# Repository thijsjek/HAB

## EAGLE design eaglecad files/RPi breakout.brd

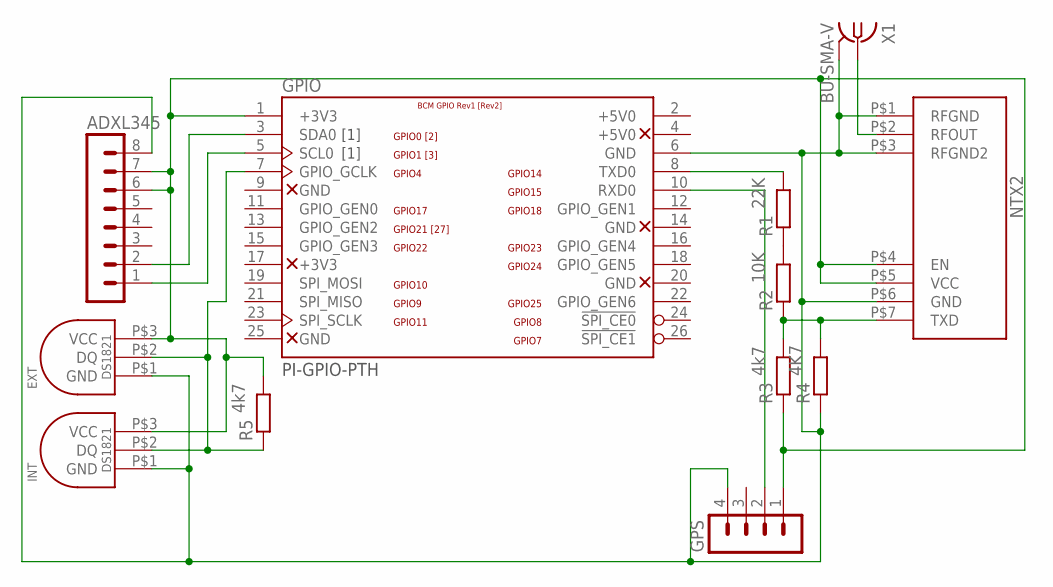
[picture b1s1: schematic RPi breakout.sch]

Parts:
ADXL345: MA08-1
EXT: DS1821
GPIO: PI-GPIO-PTH; GPIO-CONNECTOR
GPS: MA04-1
INT: DS1821
NTX2: NTX2
R1, R2, R3, R4, R5: R-EU_0207/10; 0207/10
X1: BU-SMA-V

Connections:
+3V3: ADXL345.6, ADXL345.7, EXT.P$3 (VCC), GPIO.1 (+3V3), GPS.1, INT.P$3 (VCC), NTX2.P$4 (EN), NTX2.P$5 (VCC), R3.1, R5.2
+5V0: GPIO.2 (+5V0)
GND: ADXL345.8, EXT.P$1 (GND), GPIO.6 (GND), GPS.4, INT.P$1 (GND), NTX2.P$1 (RFGND), NTX2.P$3 (RFGND2), NTX2.P$6 (GND), R4.1, X1.2, X1.3 (2), X1.4 (2), X1.5 (2)
unnamed: GPIO.10 (RXD0), GPS.2
unnamed: GPIO.8 (TXD0), R1.2
unnamed: NTX2.P$7 (TXD), R2.1, R3.2, R4.2
unnamed: NTX2.P$2 (RFOUT), X1.1
unnamed: R1.1, R2.2
unnamed: ADXL345.1, GPIO.5 (SCL0)
unnamed: ADXL345.2, GPIO.3 (SDA0)
unnamed: EXT.P$2 (DQ), GPIO.7 (GPIO_GCLK), INT.P$2 (DQ), R5.1

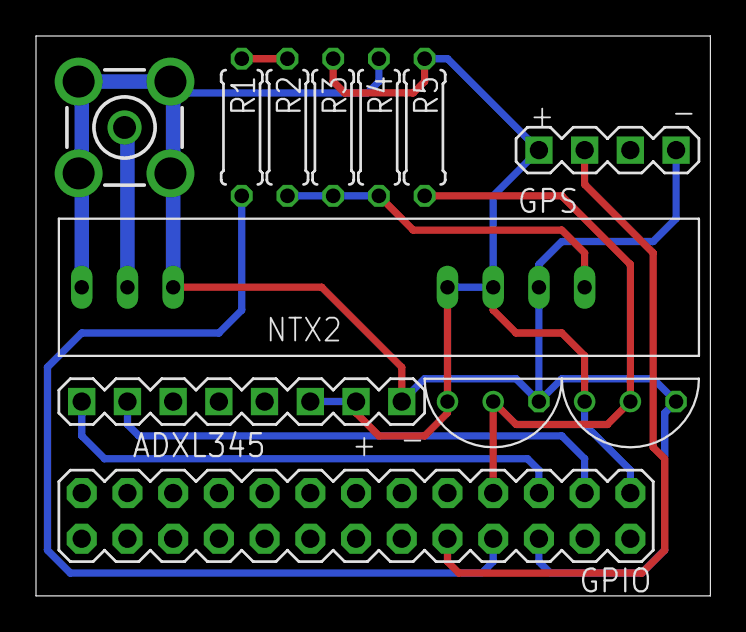
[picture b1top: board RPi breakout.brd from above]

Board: 2 copper layers, 37.5 x 31.1 mm, 12 parts (0 on the bottom side), 10 nets.

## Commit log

2014-01-21 Update temperature.py
    Changed output format to match for a .csv file
2016-04-22 Delete temperature.py
    Added the measurements into transmit.py
2016-04-22 Delete ntx2.py
    merged the temperature, gps and ntx into transmit.py
2016-04-23 Added files via upload
2016-04-23 Delete GPS.py
    obsolete, we log the gps data over the radio
2016-04-23 Added files via upload
    Stand alone temperature script, with output in a .csv file.
